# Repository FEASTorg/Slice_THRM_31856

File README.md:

<div align="center">
  <!-- Title: -->
  
  <h2><a href="https://github.com/uwo-fast/Slice_THRM"> Slice THRM </a></h2>
  <!-- Labels: -->
  <!-- First row: -->

  <a href="https://certification.oshwa.org/">
    
    <!-- img src="https://img.shields.io/badge/OSHWA-Certified-darkgreen?style=flat-square" height="20" alt="OSHWA" -->       <!-- img src="https://img.shields.io/badge/OSHWA-Pending-darkorange?style=flat-square" height="20" alt="OSHWA" -->
  </a>

  <!-- Second row: -->
  <br>

  <!-- Short description: -->
  <h3>Thermocouple Reader Slice for BREAD.</h3>
</div>

## Introduction
[Provide a brief introduction to the project, including the motivation and goals. Explain the significance and context of the research.]

## Project Overview
[Describe the project in more detail. This section can be split into subsections if necessary.]

## Installation
[Provide instructions for installing any necessary software or hardware components.]

## Usage
[Explain how to use the project. Include examples and screenshots if applicable.]

### Basic Usage
[Provide basic usage instructions.]

### Advanced Usage
[Provide advanced usage instructions, including any optional features or configurations.]

## Documentation
[Link to the detailed documentation if available. Provide instructions on how to access and navigate the documentation.]

## Contributing
[Explain how others can contribute to the project. Include guidelines for submitting issues, pull requests, and any coding standards.]

### Code of Conduct
[Link to the project's code of conduct if available.]

## License
[State the license under which the project is distributed. Include a link to the full license text.]

## Acknowledgements
[Acknowledge any contributors, collaborators, funding sources, or organizations that supported the project.]

## Contact
[Provide contact information for the project maintainer(s) or lead researcher(s). Include an email address or a link to a contact form.]

---

<div align="center">
  
</div>

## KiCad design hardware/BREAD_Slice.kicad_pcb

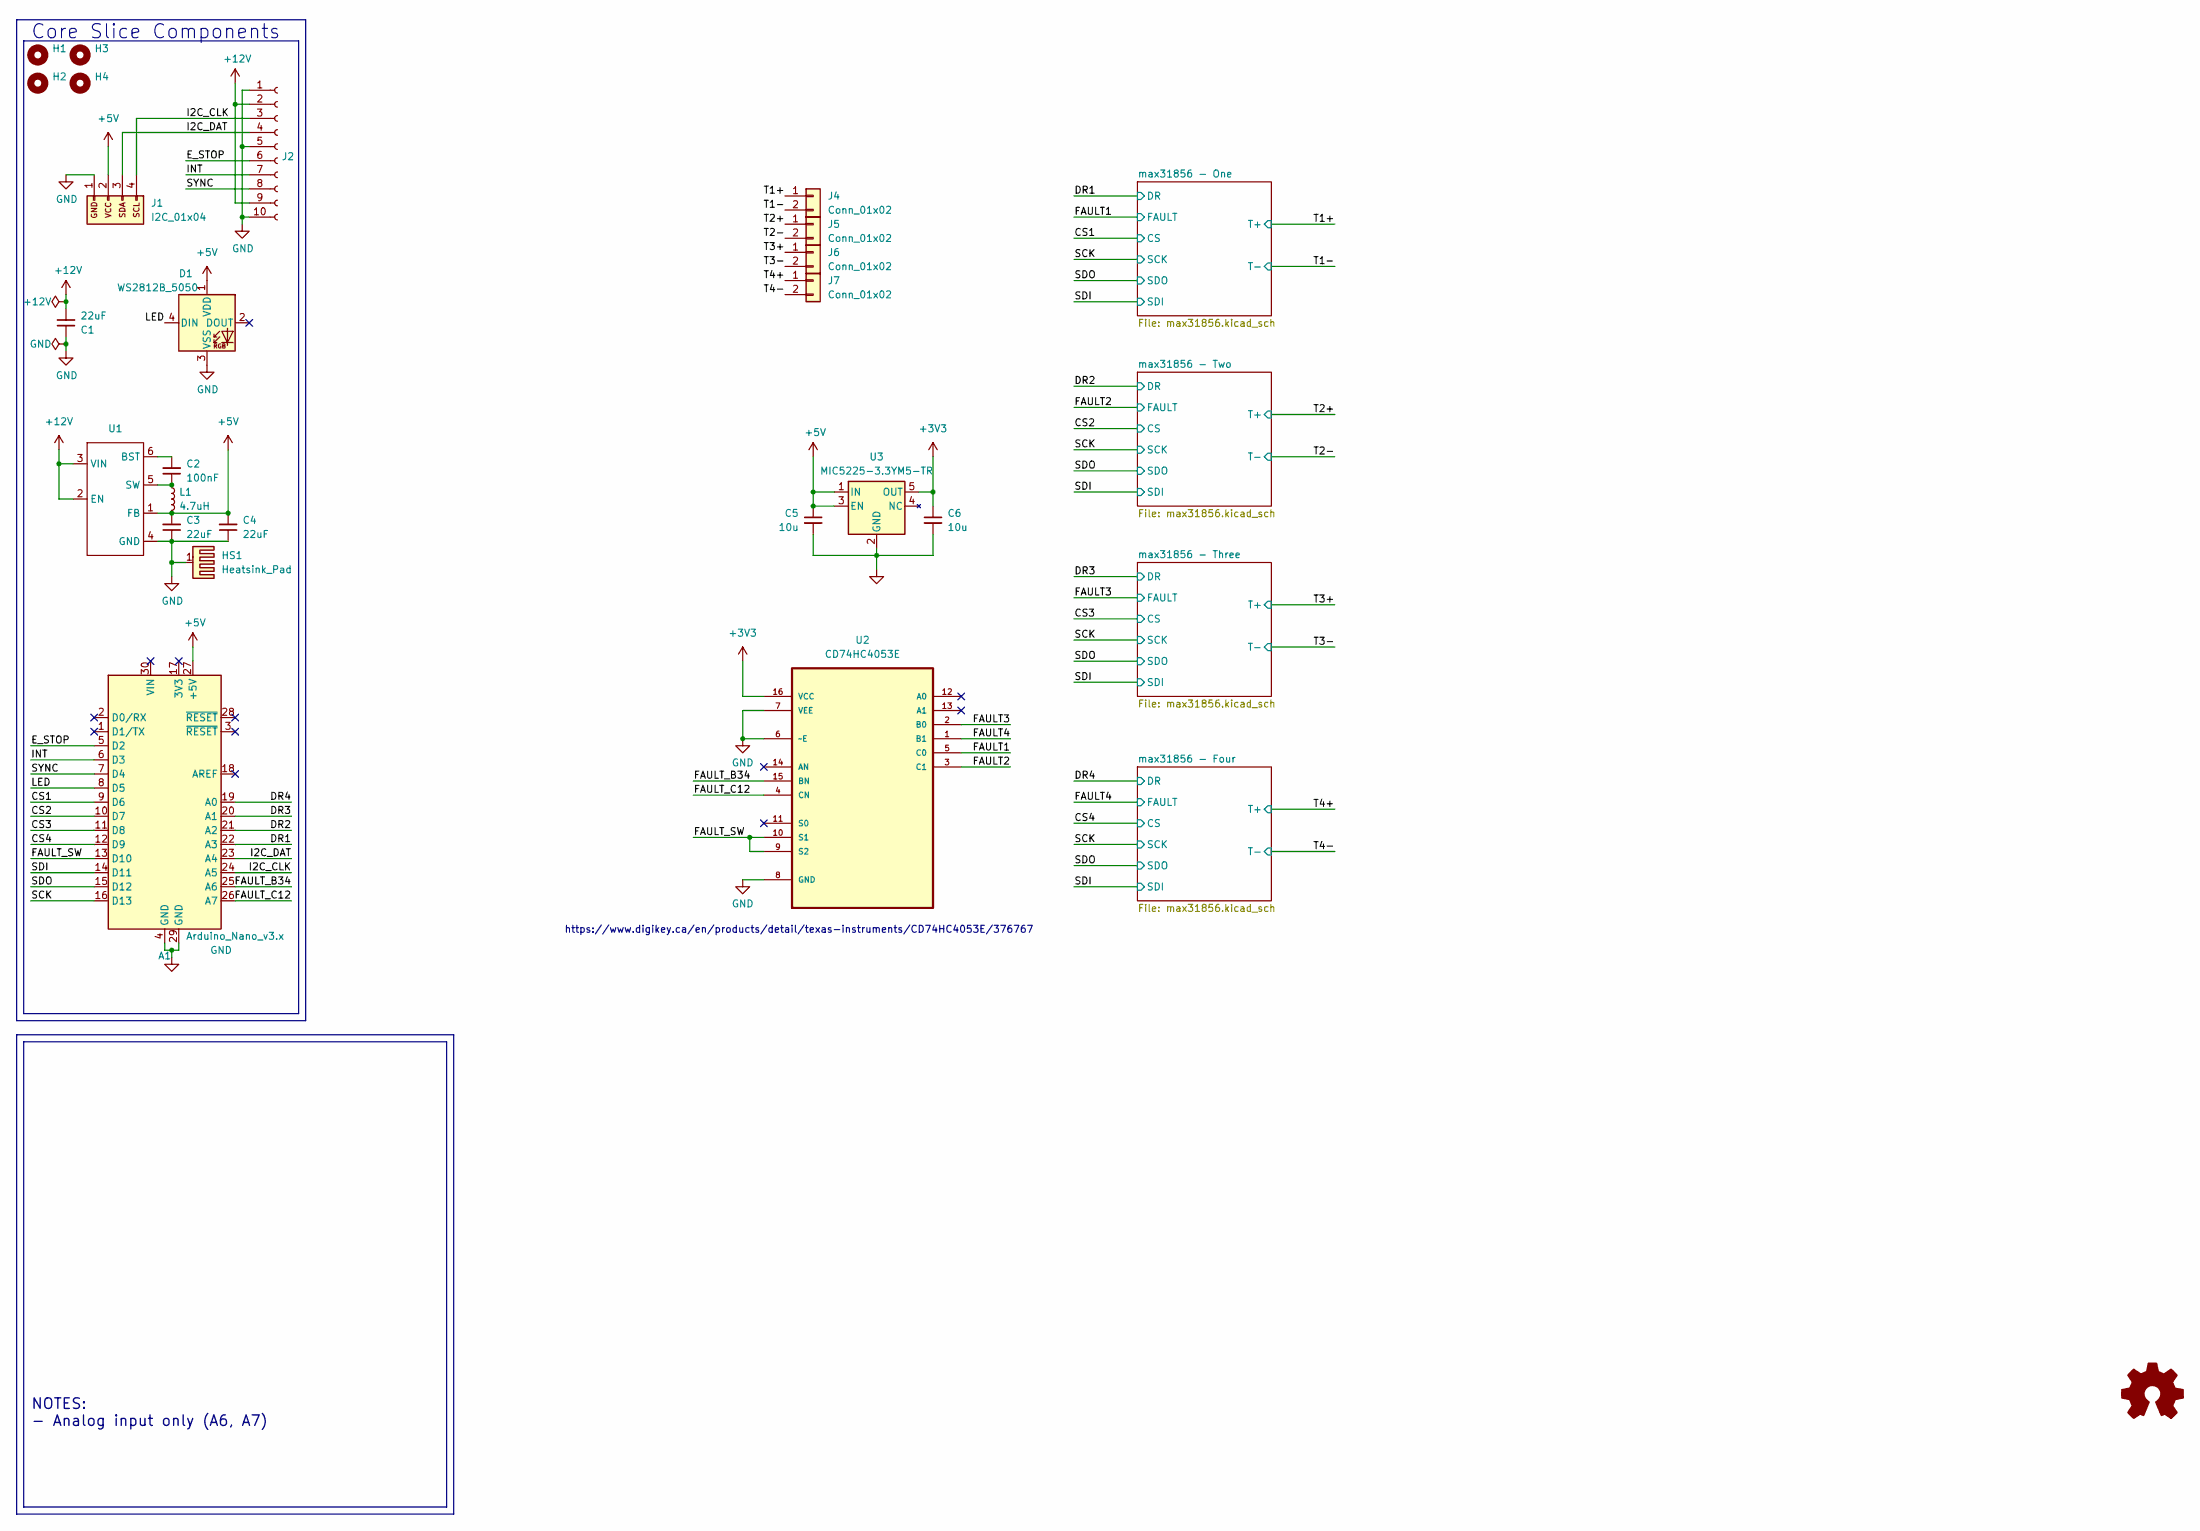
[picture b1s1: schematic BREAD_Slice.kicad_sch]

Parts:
A1: Arduino_Nano_v3.x; Arduino_Nano
C1, C3, C4: 22uF; C_1206_3216Metric
C2: 100nF; C_1206_3216Metric
C5, C6: 10u; C_1206_3216Metric
D1: WS2812B_5050; WS2812-5050-4PIN
H1, H2, H3, H4: MountingHole; MountingHole_5mm
HS1: Heatsink_Pad; Thermal_Pad
J1: I2C_01x04; JST_SH_SM04B-SRSS-TB_1x04-1MP_P1.00mm_Horizontal
J2: Conn_01x10_Female; PinSocket_1x10_P2.54mm_Horizontal
J4, J5, J6, J7: Conn_01x02; TerminalBlock_4Ucon_1x02_P3.50mm_Horizontal
L1: 4.7uH; L_1210_3225Metric
U1: TSOT-23-6
U2: CD74HC4053E; DIP254P762X508-16; MPN CD74HC4053E
U3: MIC5225-3.3YM5-TR; SOT-23-5

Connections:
+3V3: C6.1, U2.16 (VCC), U3.5 (OUT); also elsewhere on the board
+5V: A1.27 (+5V), C3.2, C4.2, C5.1, D1.1 (VDD), J1.2, L1.2, U1.1 (FB), U3.1 (IN), U3.3 (EN)
+12V: C1.2, J2.2, J2.9, U1.2 (EN), U1.3 (VIN)
/CS1: A1.9 (D6); also elsewhere on the board
/CS2: A1.10 (D7); also elsewhere on the board
/CS3: A1.11 (D8); also elsewhere on the board
/CS4: A1.12 (D9); also elsewhere on the board
/DR1: A1.22 (A3); also elsewhere on the board
/DR2: A1.21 (A2); also elsewhere on the board
/DR3: A1.20 (A1); also elsewhere on the board
/DR4: A1.19 (A0); also elsewhere on the board
/E_STOP: A1.5 (D2), J2.6
/FAULT1: U2.5 (C0); also elsewhere on the board
/FAULT2: U2.3 (C1); also elsewhere on the board
/FAULT3: U2.2 (B0); also elsewhere on the board
/FAULT4: U2.1 (B1); also elsewhere on the board
/FAULT_B34: A1.25 (A6), U2.15 (BN)
/FAULT_C12: A1.26 (A7), U2.4 (CN)
/FAULT_SW: A1.13 (D10), U2.9 (S2), U2.10 (S1)
/I2C_CLK: A1.24 (A5), J1.4, J2.3
/I2C_DAT: A1.23 (A4), J1.3, J2.4
/INT: A1.6 (D3), J2.7
/LED: A1.8 (D5), D1.4 (DIN)
/SCK: A1.16 (D13); also elsewhere on the board
/SDI: A1.14 (D11); also elsewhere on the board
/SDO: A1.15 (D12); also elsewhere on the board
/SYNC: A1.7 (D4), J2.8
/T1+: J4.1; also elsewhere on the board
/T1-: J4.2; also elsewhere on the board
/T2+: J5.1; also elsewhere on the board
/T2-: J5.2; also elsewhere on the board
/T3+: J6.1; also elsewhere on the board
/T3-: J6.2; also elsewhere on the board
/T4+: J7.1; also elsewhere on the board
/T4-: J7.2; also elsewhere on the board
GND: A1.4 (GND), A1.29 (GND), C1.1, C3.1, C4.1, C5.2, C6.2, D1.3 (VSS), HS1.1, J1.1, J2.1, J2.5, J2.10, U1.4 (GND), U2.6 (~E), U2.7 (VEE), U2.8 (GND), U3.2 (GND); also elsewhere on the board
unnamed: C2.2, U1.6 (BST)
unnamed: C2.1, L1.1, U1.5 (SW)

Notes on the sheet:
NOTES: - Analog input only (A6, A7)
Core Slice Components
https://www.digikey.ca/en/products/detail/texas-instruments/CD74HC4053E/376767

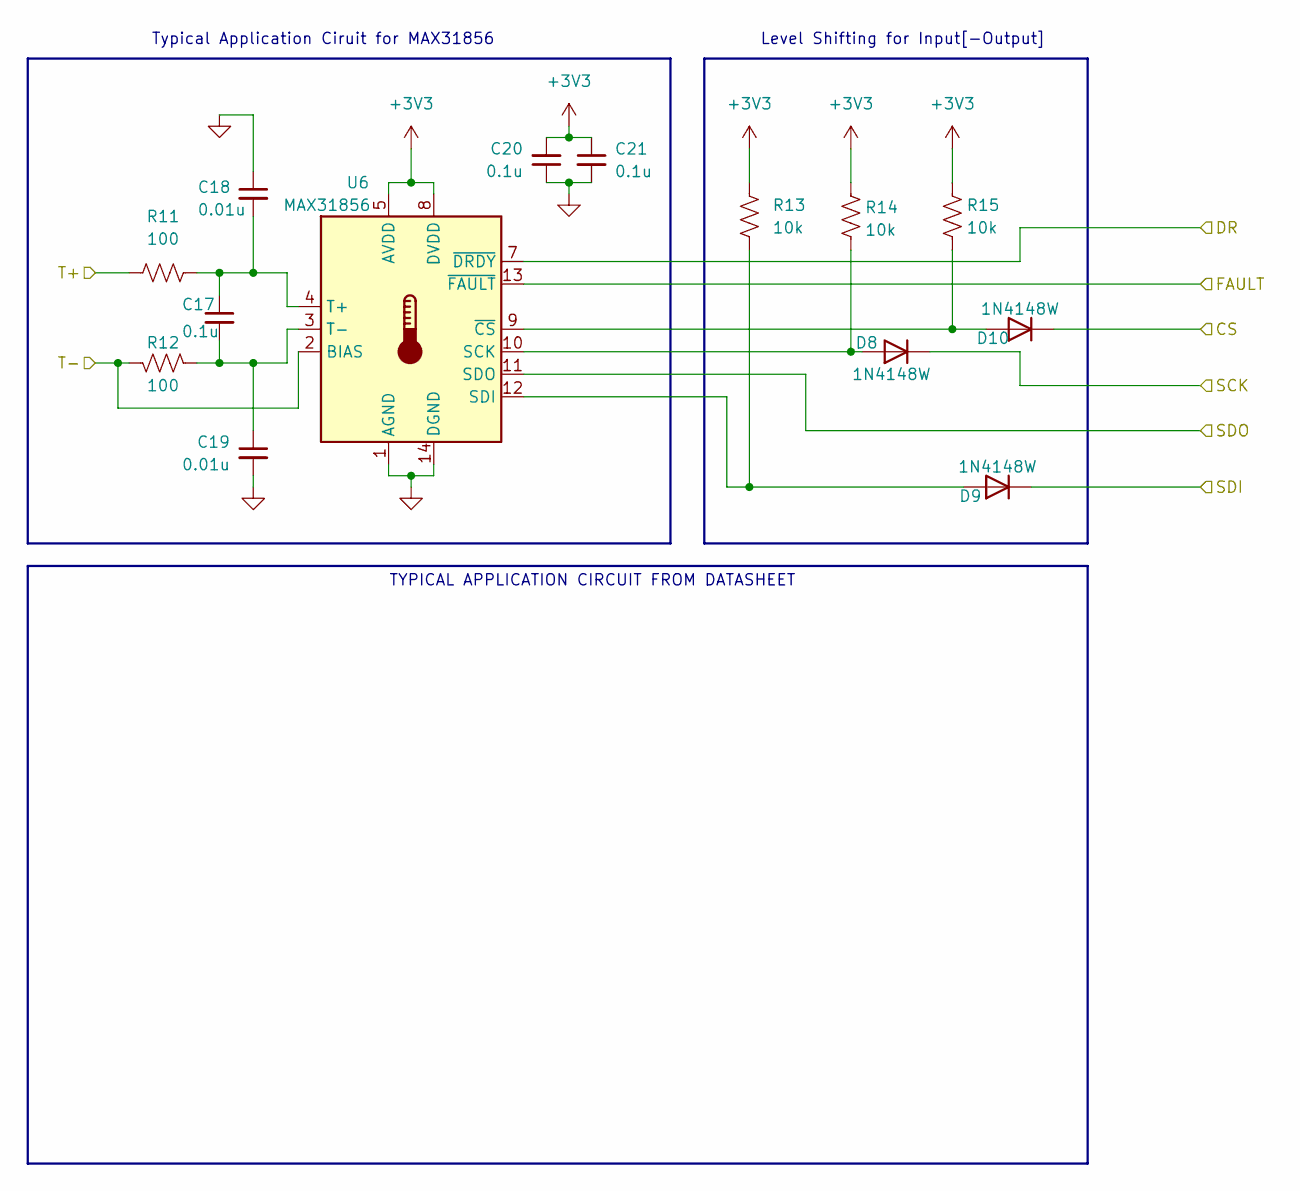
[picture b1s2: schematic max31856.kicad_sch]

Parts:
C17, C20, C21: 0.1u; C_1206_3216Metric
C18, C19: 0.01u; C_1206_3216Metric
D8, D9, D10: 1N4148W; D_SOD-123
R11, R12: 100; R_1206_3216Metric
R13, R14, R15: 10k; R_1206_3216Metric
U6: MAX31856; TSSOP-14_4.4x5mm_P0.65mm

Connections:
+3V3: C20.2, C21.1, R13.1, R14.1, R15.1, U6.5 (AVDD), U6.8 (DVDD); also elsewhere on the board
/CS3: D10.1 (K); also elsewhere on the board
/DR3: U6.7 (~DRDY); also elsewhere on the board
/FAULT3: U6.13 (~FAULT); also elsewhere on the board
/SCK: D8.1 (K); also elsewhere on the board
/SDI: D9.1 (K); also elsewhere on the board
/SDO: U6.11 (SDO); also elsewhere on the board
/T3+: R11.1; also elsewhere on the board
/T3-: R12.1, U6.2 (BIAS); also elsewhere on the board
GND: C18.1, C19.2, C20.1, C21.2, U6.1 (AGND), U6.14 (DGND); also elsewhere on the board
unnamed: D8.2 (A), R14.2, U6.10 (SCK)
unnamed: D9.2 (A), R13.2, U6.12 (SDI)
unnamed: D10.2 (A), R15.2, U6.9 (~CS)
unnamed: C17.1, C18.2, R11.2, U6.4 (T+)
unnamed: C17.2, C19.1, R12.2, U6.3 (T-)

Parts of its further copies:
C7, C10, C11, C12, C15, C16, C22, C25, C26: 0.1u; C_1206_3216Metric
C8, C9, C13, C14, C23, C24: 0.01u; C_1206_3216Metric
D2, D3, D4, D5, D6, D7, D11, D12, D13: 1N4148W; D_SOD-123
R1, R2, R6, R7, R16, R17: 100; R_1206_3216Metric
R3, R4, R5, R8, R9, R10, R18, R19, R20: 10k; R_1206_3216Metric
U4, U5, U7: MAX31856; TSSOP-14_4.4x5mm_P0.65mm

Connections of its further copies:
+3V3: C10.2, C11.1, C15.2, C16.1, C25.2, C26.1, R3.1, R4.1, R5.1, R8.1, R9.1, R10.1, R18.1, R19.1, R20.1, U4.5 (AVDD), U4.8 (DVDD), U5.5 (AVDD), U5.8 (DVDD), U7.5 (AVDD), U7.8 (DVDD); also elsewhere on the board
/CS1: D4.1 (K); also elsewhere on the board
/CS2: D7.1 (K); also elsewhere on the board
/CS4: D13.1 (K); also elsewhere on the board
/DR1: U4.7 (~DRDY); also elsewhere on the board
/DR2: U5.7 (~DRDY); also elsewhere on the board
/DR4: U7.7 (~DRDY); also elsewhere on the board
/FAULT1: U4.13 (~FAULT); also elsewhere on the board
/FAULT2: U5.13 (~FAULT); also elsewhere on the board
/FAULT4: U7.13 (~FAULT); also elsewhere on the board
/SCK: D2.1 (K), D5.1 (K), D11.1 (K); also elsewhere on the board
/SDI: D3.1 (K), D6.1 (K), D12.1 (K); also elsewhere on the board
/SDO: U4.11 (SDO), U5.11 (SDO), U7.11 (SDO); also elsewhere on the board
/T1+: R1.1; also elsewhere on the board
/T1-: R2.1, U4.2 (BIAS); also elsewhere on the board
/T2+: R6.1; also elsewhere on the board
/T2-: R7.1, U5.2 (BIAS); also elsewhere on the board
/T4+: R16.1; also elsewhere on the board
/T4-: R17.1, U7.2 (BIAS); also elsewhere on the board
GND: C8.1, C9.2, C10.1, C11.2, C13.1, C14.2, C15.1, C16.2, C23.1, C24.2, C25.1, C26.2, U4.1 (AGND), U4.14 (DGND), U5.1 (AGND), U5.14 (DGND), U7.1 (AGND), U7.14 (DGND); also elsewhere on the board
unnamed: D2.2 (A), R4.2, U4.10 (SCK)
unnamed: D3.2 (A), R3.2, U4.12 (SDI)
unnamed: D4.2 (A), R5.2, U4.9 (~CS)
unnamed: D5.2 (A), R9.2, U5.10 (SCK)
unnamed: D6.2 (A), R8.2, U5.12 (SDI)
unnamed: D7.2 (A), R10.2, U5.9 (~CS)
unnamed: D11.2 (A), R19.2, U7.10 (SCK)
unnamed: D12.2 (A), R18.2, U7.12 (SDI)
unnamed: D13.2 (A), R20.2, U7.9 (~CS)
unnamed: C7.1, C8.2, R1.2, U4.4 (T+)
unnamed: C7.2, C9.1, R2.2, U4.3 (T-)
unnamed: C12.1, C13.2, R6.2, U5.4 (T+)
unnamed: C12.2, C14.1, R7.2, U5.3 (T-)
unnamed: C22.1, C23.2, R16.2, U7.4 (T+)
unnamed: C22.2, C24.1, R17.2, U7.3 (T-)

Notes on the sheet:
Level Shifting for Input[-Output]
Typical Application Ciruit for MAX31856
TYPICAL APPLICATION CIRCUIT FROM DATASHEET

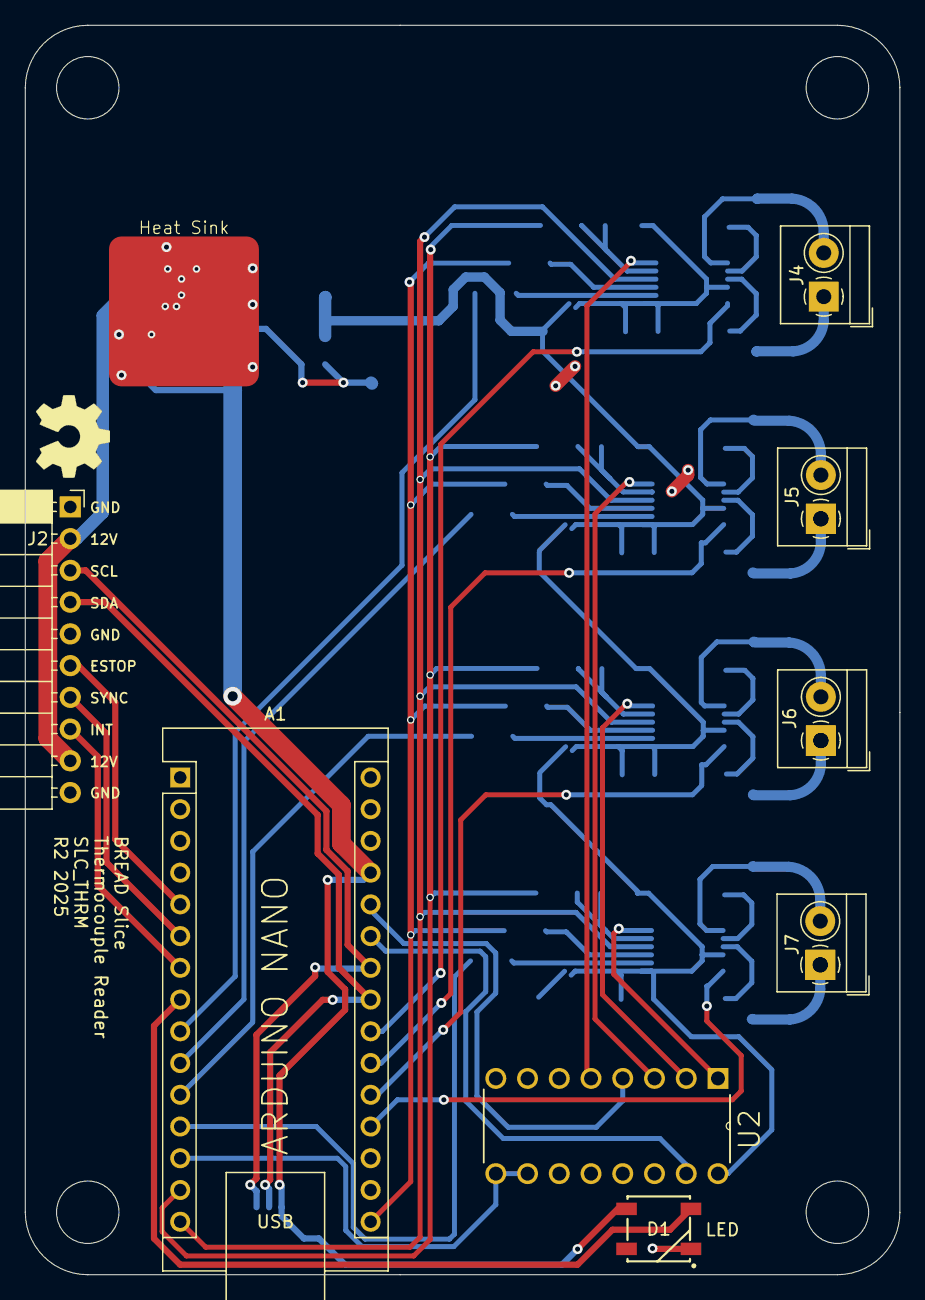
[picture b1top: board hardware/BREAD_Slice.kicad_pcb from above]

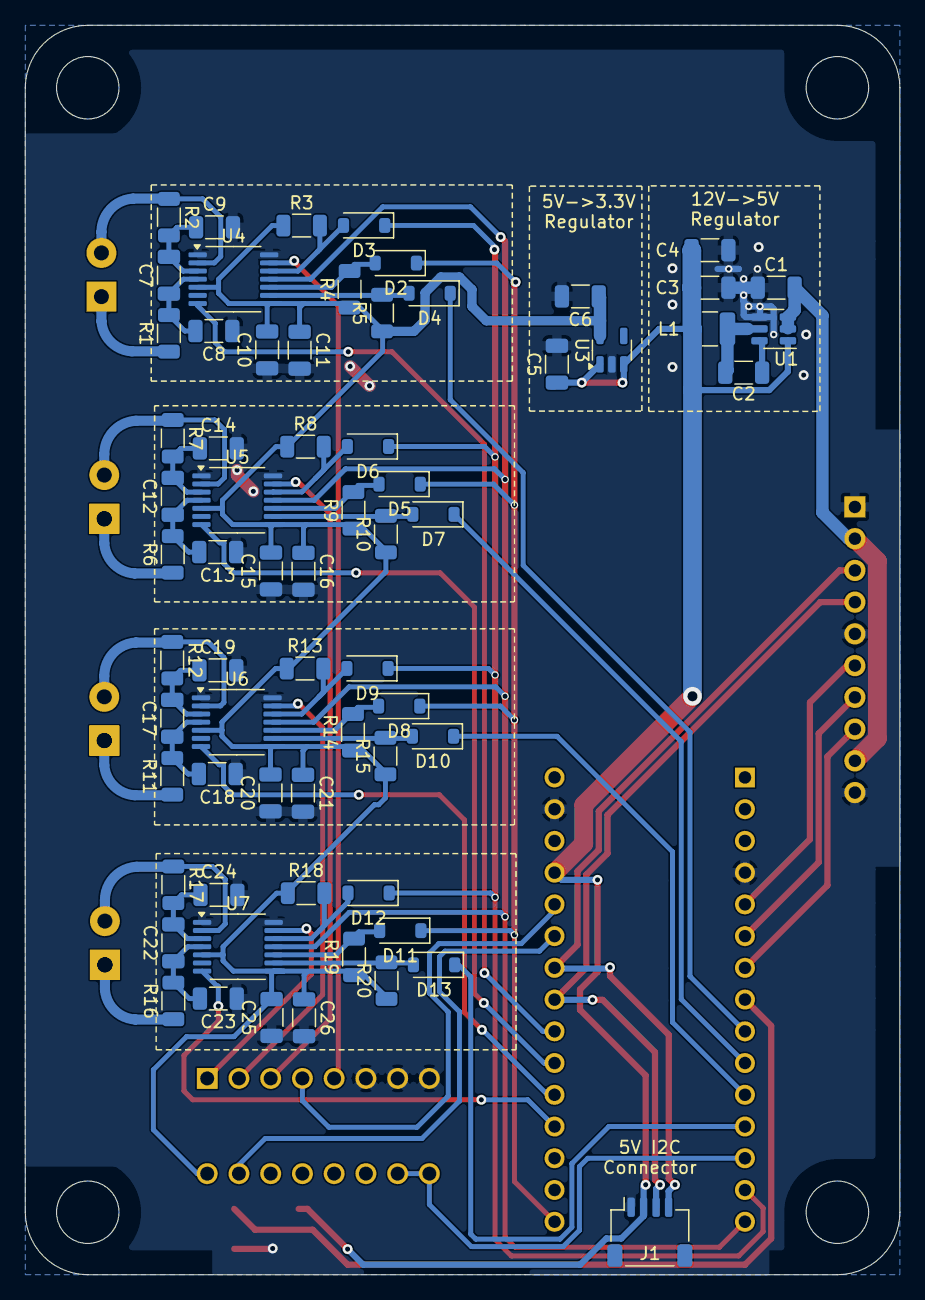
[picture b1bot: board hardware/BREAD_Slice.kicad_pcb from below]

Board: 2 copper layers, 70.0 x 100.0 mm, 80 parts (66 on the bottom side), 58 nets.

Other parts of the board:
Logo1: Logo_Open_Hardware_Small; OSHW-Symbol_6.7x6mm_SilkScreen

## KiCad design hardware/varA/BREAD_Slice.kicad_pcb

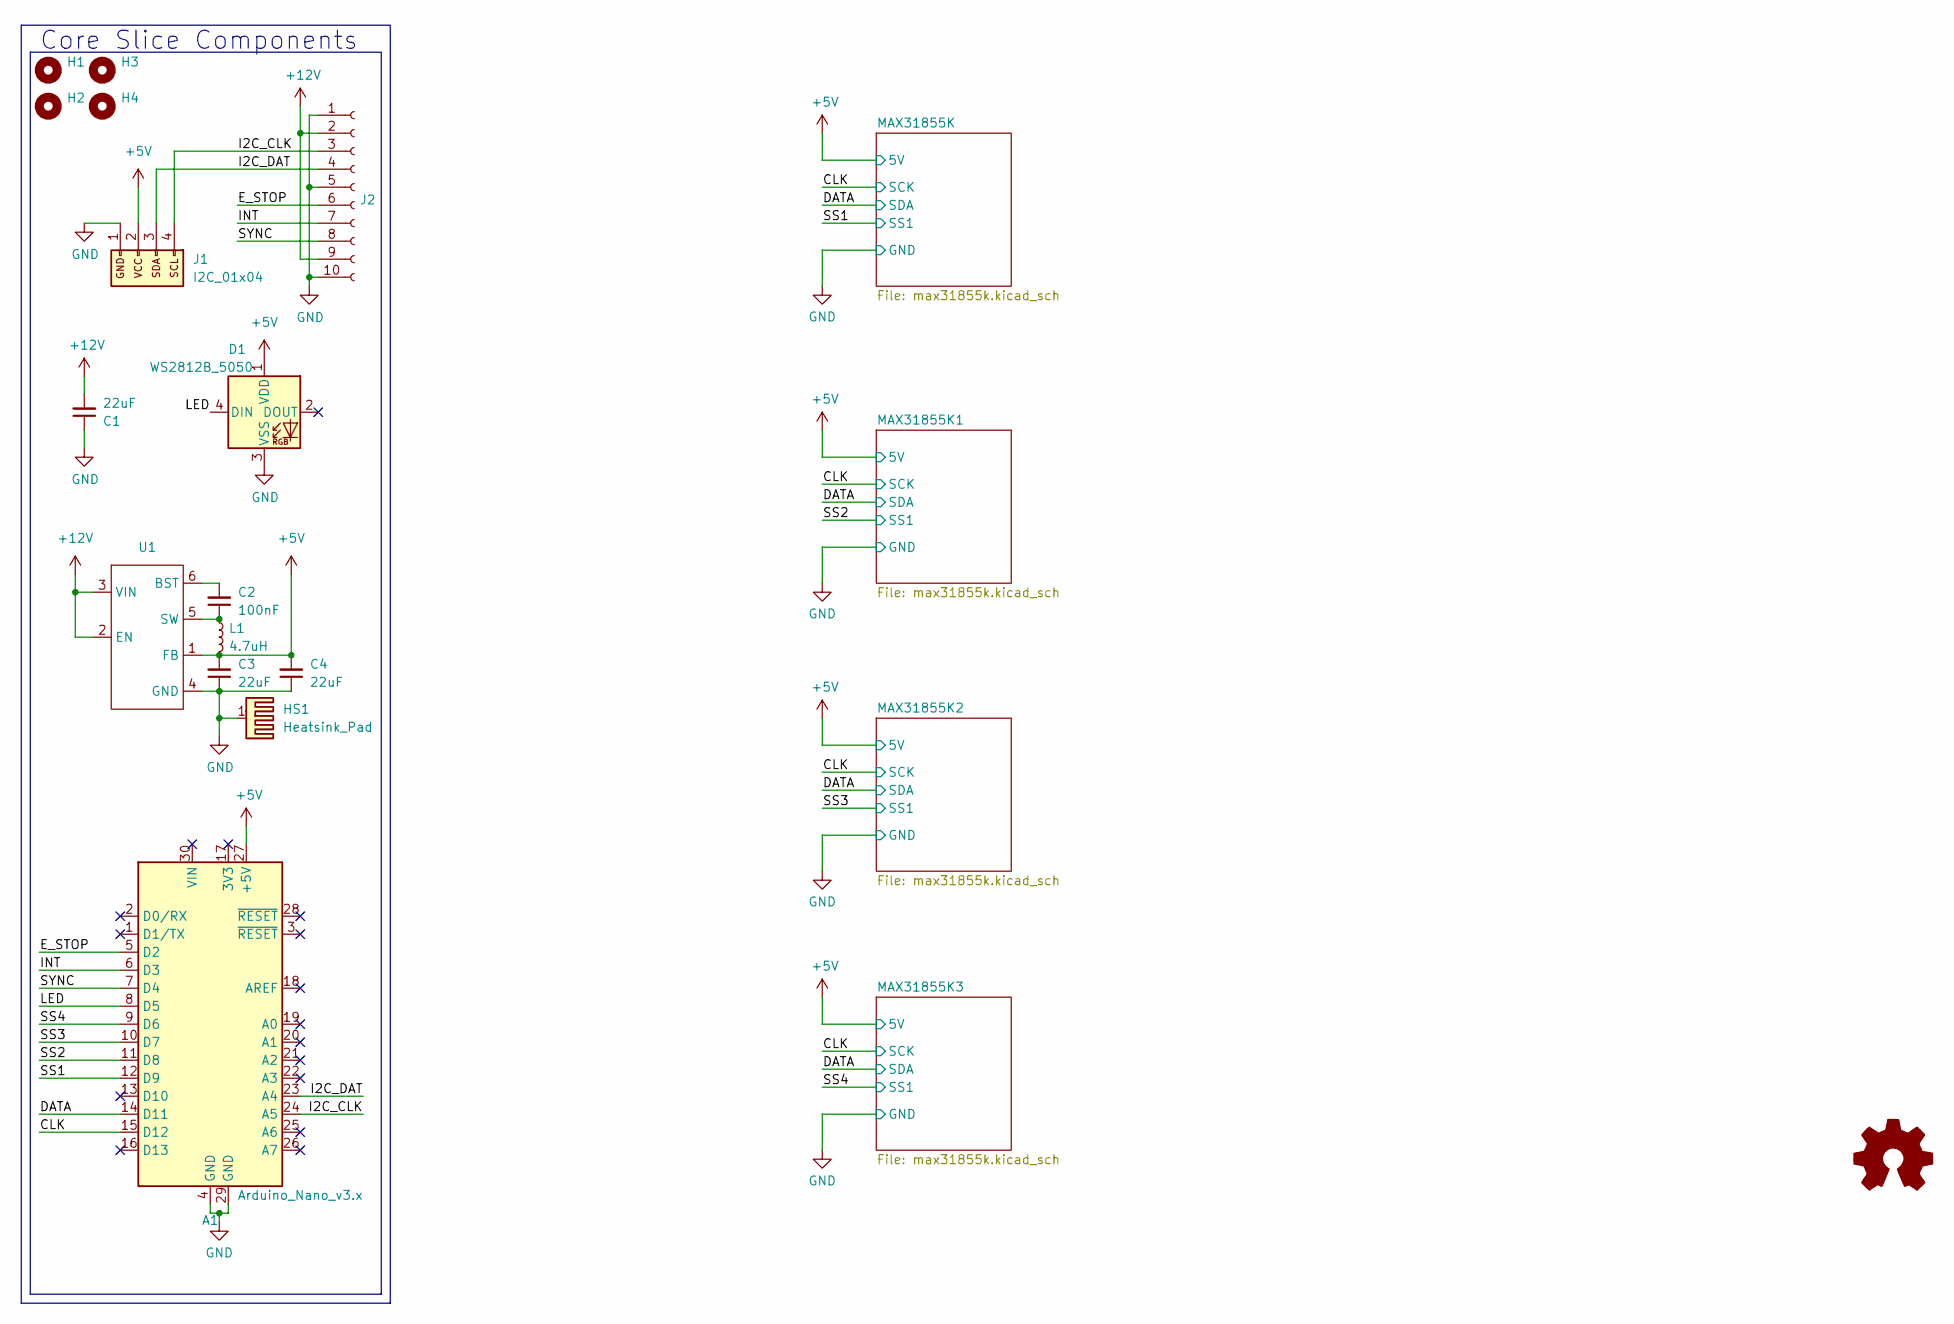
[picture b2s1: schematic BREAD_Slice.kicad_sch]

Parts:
A1: Arduino_Nano_v3.x; Arduino_Nano
C1, C3, C4: 22uF; C_1206_3216Metric
C2: 100nF; C_1206_3216Metric
D1: WS2812B_5050; WS2812-5050-4PIN
H1, H2, H3, H4: MountingHole; MountingHole_5mm
HS1: Heatsink_Pad; Thermal Pad
J1: I2C_01x04; JST_SH_SM04B-SRSS-TB_1x04-1MP_P1.00mm_Horizontal
J2: Conn_01x10_Female; PinSocket_1x10_P2.54mm_Horizontal
L1: 4.7uH; L_1210_3225Metric
U1: TSOT-23-6

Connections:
+5V: A1.27 (+5V), C3.2, C4.2, D1.1 (VDD), J1.2, L1.2, U1.1 (FB); also elsewhere on the board
+12V: C1.2, J2.2, J2.9, U1.2 (EN), U1.3 (VIN)
/CLK: A1.15 (D12); also elsewhere on the board
/DATA: A1.14 (D11); also elsewhere on the board
/E_STOP: A1.5 (D2), J2.6
/I2C_CLK: A1.24 (A5), J1.4, J2.3
/I2C_DAT: A1.23 (A4), J1.3, J2.4
/INT: A1.6 (D3), J2.7
/LED: A1.8 (D5), D1.4 (DIN)
/SS1: A1.12 (D9); also elsewhere on the board
/SS2: A1.11 (D8); also elsewhere on the board
/SS3: A1.10 (D7); also elsewhere on the board
/SS4: A1.9 (D6); also elsewhere on the board
/SYNC: A1.7 (D4), J2.8
GND: A1.4 (GND), A1.29 (GND), C1.1, C3.1, C4.1, D1.3 (VSS), HS1.1, J1.1, J2.1, J2.5, J2.10, U1.4 (GND); also elsewhere on the board
unnamed: C2.2, U1.6 (BST)
unnamed: C2.1, L1.1, U1.5 (SW)

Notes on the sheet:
Core Slice Components

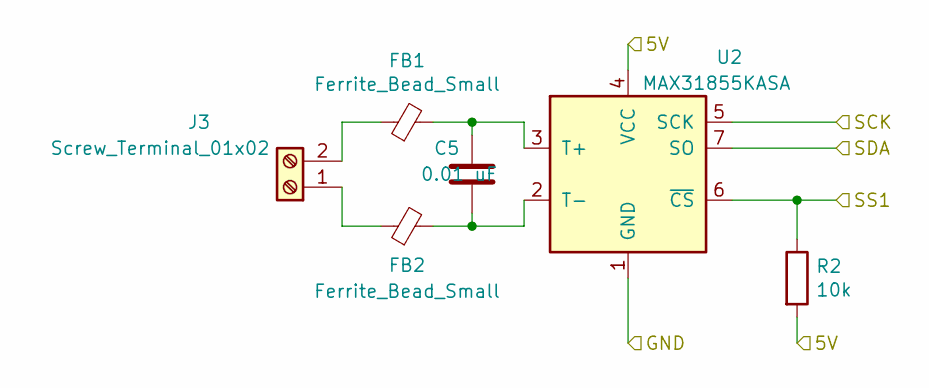
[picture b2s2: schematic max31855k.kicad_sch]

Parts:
C5: 0.01 uF; C_1206_3216Metric_Pad1.33x1.80mm_HandSolder
FB1, FB2: Ferrite_Bead_Small; R_1206_3216Metric_Pad1.30x1.75mm_HandSolder
J3: Screw_Terminal_01x02; TerminalBlock_TE_282834-2_1x02_P2.54mm_Horizontal
R2: 10k; R_1206_3216Metric_Pad1.30x1.75mm_HandSolder
U2: MAX31855KASA; SOIC-8_3.9x4.9mm_P1.27mm

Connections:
+5V: R2.2, U2.4 (VCC); also elsewhere on the board
/CLK: U2.5 (SCK); also elsewhere on the board
/DATA: U2.7 (SO); also elsewhere on the board
/SS1: R2.1, U2.6 (~CS); also elsewhere on the board
GND: U2.1 (GND); also elsewhere on the board
unnamed: FB2.1, J3.1
unnamed: FB1.1, J3.2
unnamed: C5.1, FB1.2, U2.3 (T+)
unnamed: C5.2, FB2.2, U2.2 (T-)

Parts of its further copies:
C6, C7, C8: 0.01 uF; C_1206_3216Metric_Pad1.33x1.80mm_HandSolder
FB3, FB4, FB5, FB6, FB7, FB8: Ferrite_Bead_Small; R_1206_3216Metric_Pad1.30x1.75mm_HandSolder
J4, J5, J6: Screw_Terminal_01x02; TerminalBlock_TE_282834-2_1x02_P2.54mm_Horizontal
R3, R4, R5: 10k; R_1206_3216Metric_Pad1.30x1.75mm_HandSolder
U3, U4, U5: MAX31855KASA; SOIC-8_3.9x4.9mm_P1.27mm

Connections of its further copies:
+5V: R3.2, R4.2, R5.2, U3.4 (VCC), U4.4 (VCC), U5.4 (VCC); also elsewhere on the board
/CLK: U3.5 (SCK), U4.5 (SCK), U5.5 (SCK); also elsewhere on the board
/DATA: U3.7 (SO), U4.7 (SO), U5.7 (SO); also elsewhere on the board
/SS2: R3.1, U3.6 (~CS); also elsewhere on the board
/SS3: R4.1, U4.6 (~CS); also elsewhere on the board
/SS4: R5.1, U5.6 (~CS); also elsewhere on the board
GND: U3.1 (GND), U4.1 (GND), U5.1 (GND); also elsewhere on the board
unnamed: FB4.1, J4.1
unnamed: FB3.1, J4.2
unnamed: FB6.1, J5.1
unnamed: FB5.1, J5.2
unnamed: FB8.1, J6.1
unnamed: FB7.1, J6.2
unnamed: C6.1, FB3.2, U3.3 (T+)
unnamed: C6.2, FB4.2, U3.2 (T-)
unnamed: C7.1, FB5.2, U4.3 (T+)
unnamed: C7.2, FB6.2, U4.2 (T-)
unnamed: C8.1, FB7.2, U5.3 (T+)
unnamed: C8.2, FB8.2, U5.2 (T-)

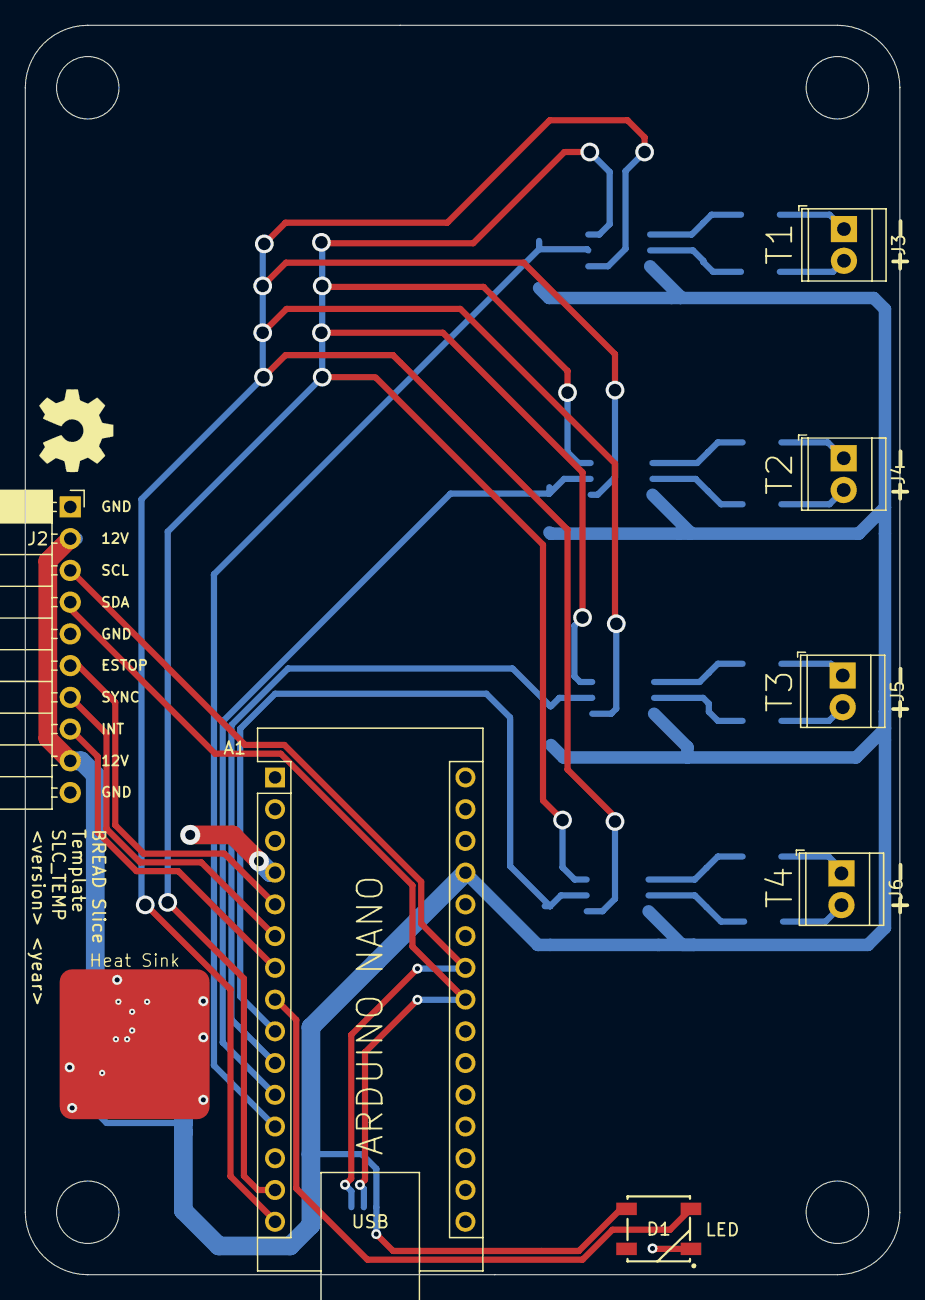
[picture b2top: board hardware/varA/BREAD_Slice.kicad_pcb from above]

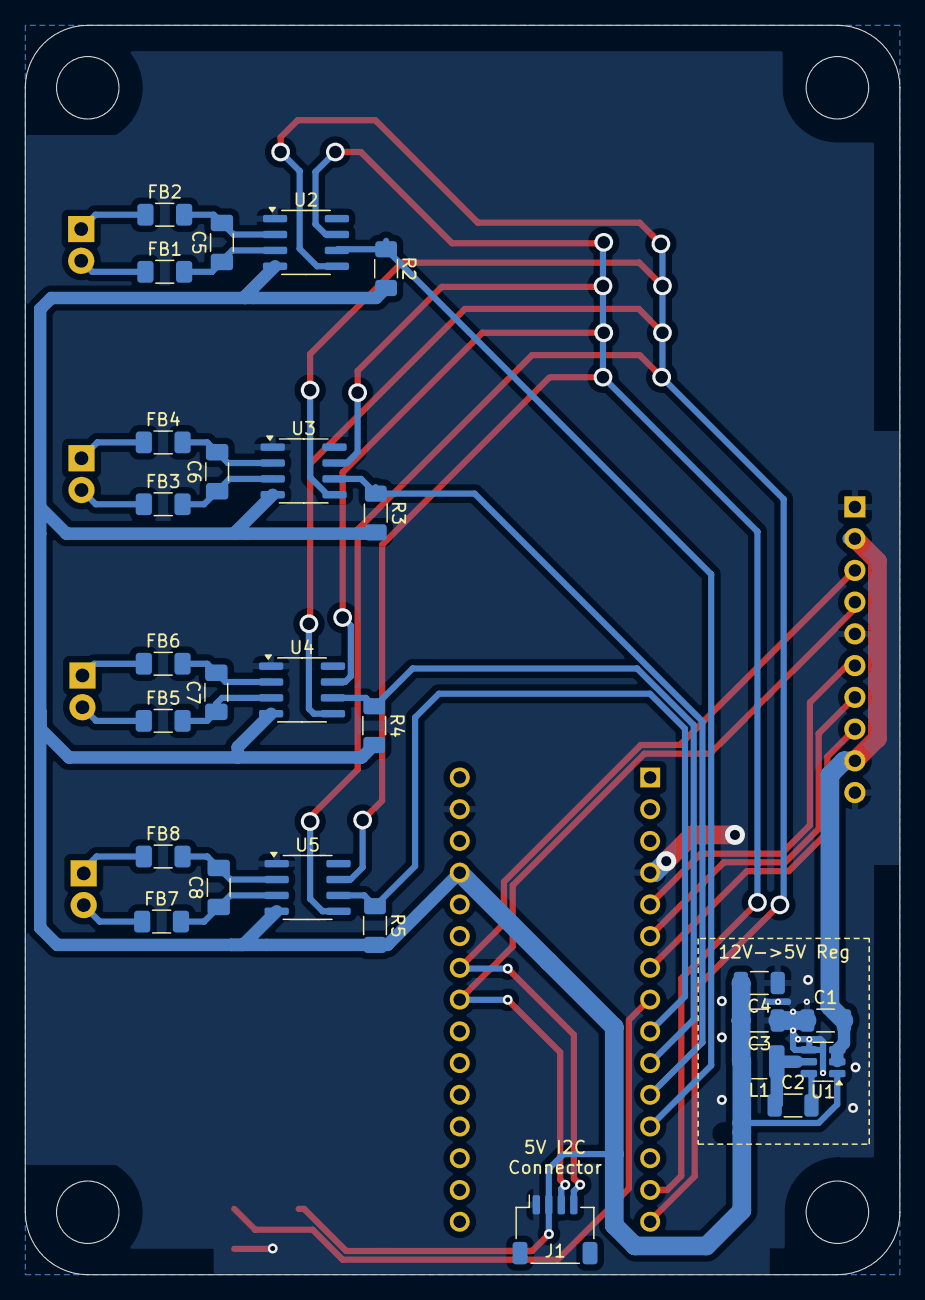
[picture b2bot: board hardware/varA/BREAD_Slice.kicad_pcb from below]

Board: 2 copper layers, 70.0 x 100.0 mm, 40 parts (27 on the bottom side), 33 nets.

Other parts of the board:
Logo1: Logo_Open_Hardware_Small; OSHW-Symbol_6.7x6mm_SilkScreen

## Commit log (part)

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2024-09-07 updated + checked schem and pcb with updated template
2024-09-12 removed unneeded top level 10k clk pull up (one on each max already
2025-04-19 minor tweaks
2025-09-25 clean out docs
2025-09-25 initial commit after split
2025-09-25 ci: add bread-infra pipeline and all docs template files
2025-09-25 hw: fix erc and drc errors; need to double check the diode and levelshift ic pathes can be independently toggled before prod
2025-09-25 📄 KiBot index + board renders (auto)
2026-04-20 refactor: org casing rename from 'FEASTorg' to 'feastorg'
2026-05-20 Add slice.yaml manifest (schema v1.0)
2026-05-24 Add TODO.md for consistency
2026-05-24 Standardize TODO.md with Pass 1/Pass 2 structure
